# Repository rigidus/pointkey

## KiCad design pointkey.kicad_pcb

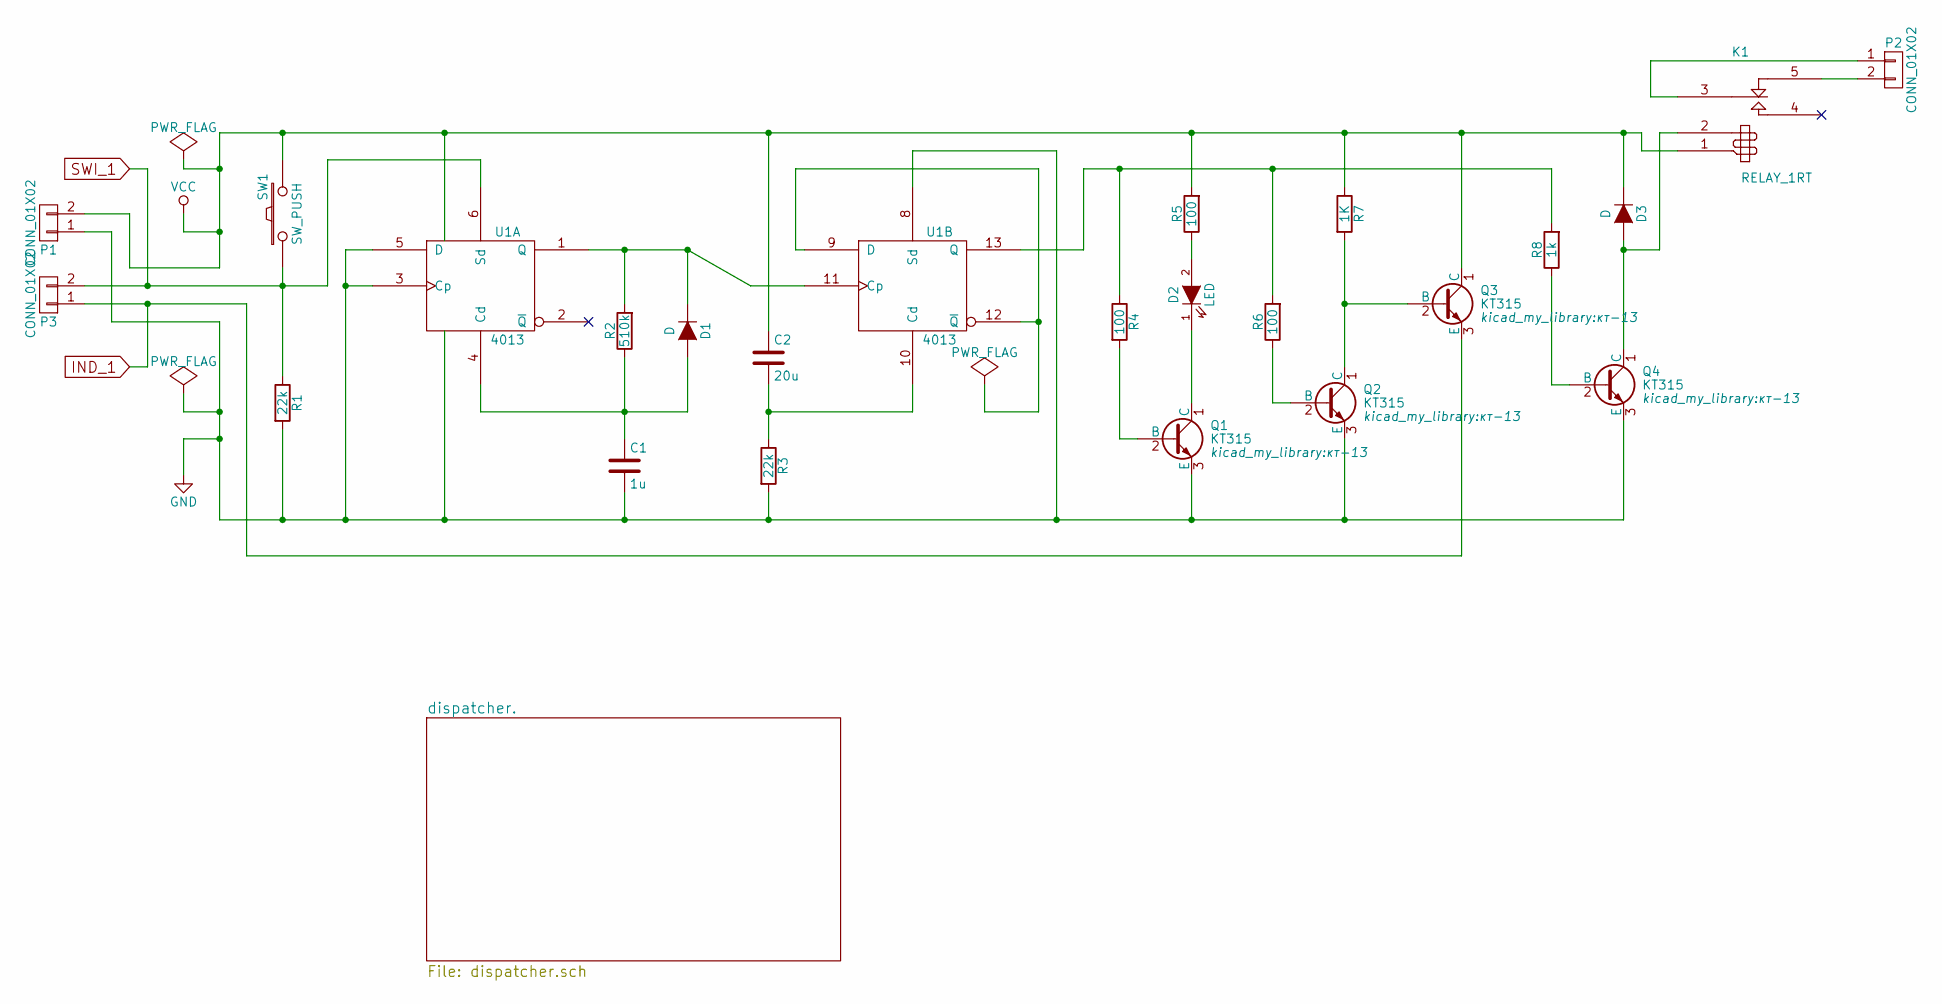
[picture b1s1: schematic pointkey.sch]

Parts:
C1: 1u; C_Radial_D5_L6_P2.5
C2: 20u; C_Radial_D5_L6_P2.5
D1, D3: D; D4
D2: LED; LED-3MM
K1: RELAY_1RT; RELAY_812H_1C_C
P1, P2, P3: CONN_01X02; AK300-2
Q1, Q2, Q3, Q4: КТ315; кт-13
R1, R3: 22k; R3-5
R2: 510k; R3-5
R4, R5, R6: 100; R3-5
R7: 1K; R3-5
R8: 1k; R3-5
SW1: SW_PUSH; SW_PUSH_SMALL
U1: 4013; DIP-14_W7.62mm

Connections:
GND: C1.2, P1.1, Q1.3 (E), Q2.3 (E), Q4.3 (E), R1.2, R3.2, U1.3 (Cp), U1.5 (D), U1.7 (VSS), U1.8 (Sd); also elsewhere on the board
IND_1: P3.1, Q3.3 (E); also elsewhere on the board
unnamed: C1.1, D1.2 (A), R2.1, U1.4 (Cd)
unnamed: C2.2, R3.1, U1.10 (Cd)
unnamed: D1.1 (K), R2.2, U1.1 (Q), U1.11 (Cp)
unnamed: D2.1 (K), Q1.1 (C)
unnamed: D2.2 (A), R5.1
unnamed: D3.2 (A), K1.2, Q4.1 (C)
unnamed: K1.3, P2.1
unnamed: K1.5, P2.2
unnamed: Q1.2 (B), R4.2
unnamed: Q2.1 (C), Q3.2 (B), R7.2
unnamed: Q2.2 (B), R6.1
unnamed: Q4.2 (B), R8.1
unnamed: R4.1, R6.2, R8.2, U1.13 (Q)
unnamed: U1.9 (D), U1.12 (~Q)
SWI_1: P3.2, R1.1, SW1.1, U1.6 (Sd); also elsewhere on the board
VCC: C2.1, D3.1 (K), K1.1, P1.2, Q3.1 (C), R5.2, R7.1, SW1.2, U1.14 (VDD); also elsewhere on the board

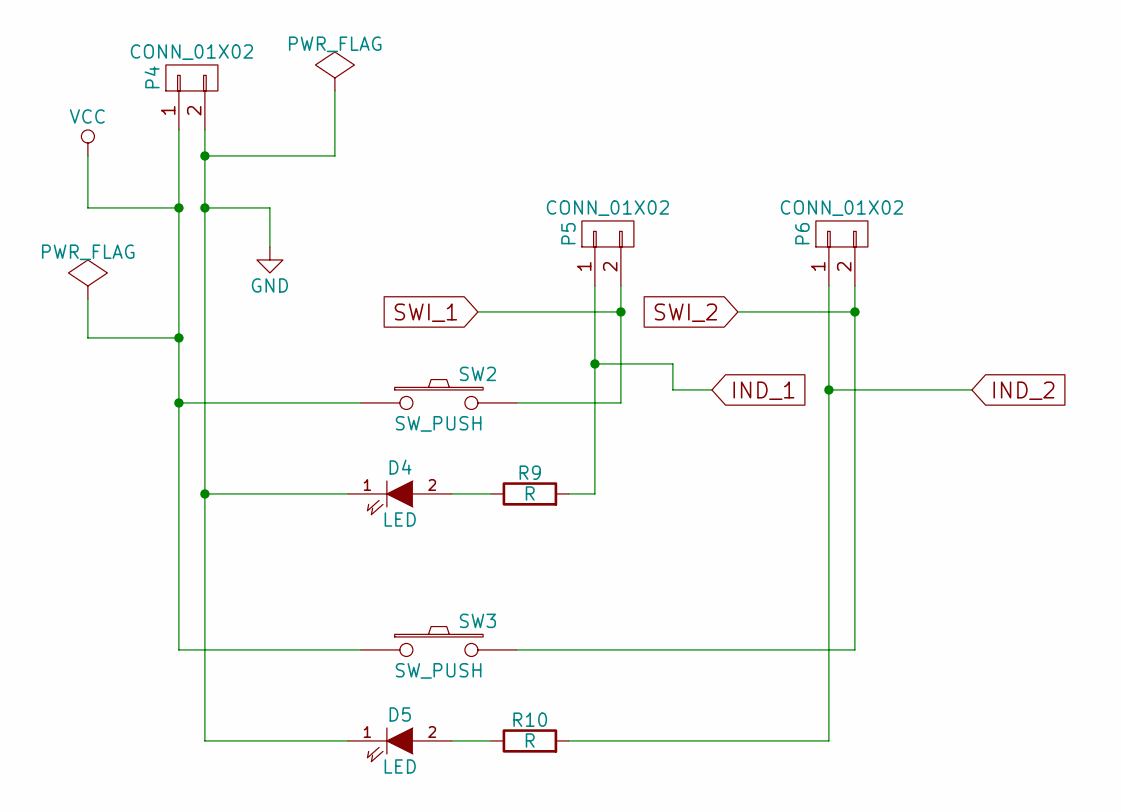
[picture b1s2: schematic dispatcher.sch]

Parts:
D4, D5: LED; LED-3MM
P4, P5, P6: CONN_01X02; AK300-2
R9, R10: R; R3-5
SW2, SW3: SW_PUSH; SW_PUSH_SMALL

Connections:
GND: D4.1 (K), D5.1 (K), P4.2; also elsewhere on the board
IND_1: P5.1, R9.2; also elsewhere on the board
IND_2: P6.1, R10.2
unnamed: D4.2 (A), R9.1
unnamed: D5.2 (A), R10.1
SWI_1: P5.2, SW2.2; also elsewhere on the board
SWI_2: P6.2, SW3.2
VCC: P4.1, SW2.1, SW3.1; also elsewhere on the board

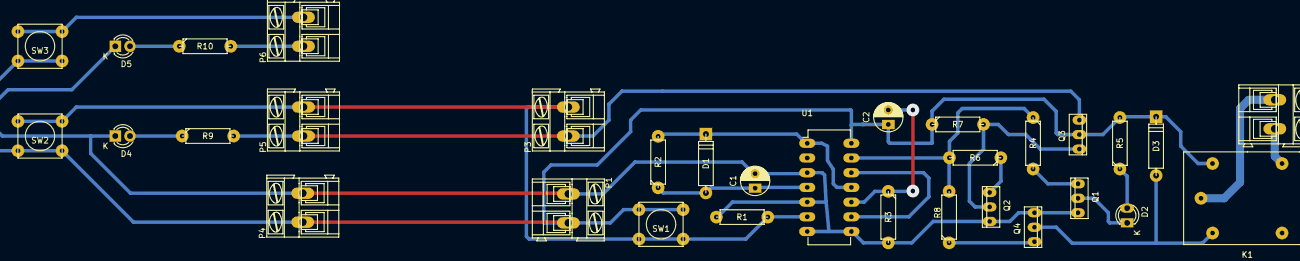
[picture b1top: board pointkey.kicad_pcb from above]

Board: 2 copper layers, 32 parts (0 on the bottom side), 22 nets.

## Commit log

2016-01-09 debounce
2016-01-09 components
2016-01-12 new pcb
2016-01-13 fixes
2016-01-14 transistor key for indicator led
2016-01-18 dispatcher
2016-01-18 release1
